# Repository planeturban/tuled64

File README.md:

# Totally Useless LED Programmer 64
### Wuuut?
It's just a useless way to use a RGB led as powerled in a C64. Why? Why not? It's pronounced TÖLP SIXTIFÅR since the author is from Sundsvall, Sweden.

# Hardware
The hardware is pretty much a stripped down Arduno Uno: an ATmega328p, an 16MHz xtal, two capacitors to piggyback on CIA2 of the C64. (The xtal and capacitors could be skipped, runnig at 8Mhz internal clock ought to be enough).

| Part | Footprint | Value |
|--|--|--|
| R1 | 1206 |Value depends on your led |
| R2 | 1206 |Value depends on your led |
| R3 |1206 |Value depends on your led |
| U1 | TQFP32 |ATMega 328P  |
| C1 | 1206 | Capacitor 22pf |
| C2 | 1206 | Capacitor 22pf |
| Y2 | HC49-US | Xtal 16MHz |

## Operation
Int1 (Arduino pin3 or ATmega pin1) is connected to  the port control (/PC) of CIA2, detecting when something is being sent from the C64 by attatching interrupt to falling state. This initializes the sequence counter interrupt function; not a pretty sight in the code, but it works. 

# Software
## 	Protocol
### Data 
| Byte | Data  |
|--|--|
|0-1  | Header: 0xff 0x99   |
| 2 | Data length, CMD + data  |
| 3 | CMD  |
| 4-n | Data, max 27 bytes  |
| n+1 | Checksum   0x100 - ((CMD + data) ^ 0xff) |

**The checksum part:**
CMD plus data is added together, xor'd and substracted from 256, let's say we're setting program speed to 10 (in blink mode: blink every 1 second). We'll be sending, header (0xff 0x99), length (0x02), set speed (0x03), speed itself (0x0a) and checksum (0x100 - ((0x03 + 0x0a) ^ 0xff) ).
| Byte | Data  |
|--|--|
|0|0xff|
|1|0x99|
|2|0x02|
|3|0x03|
|4|0x0a|
|5|0x0e|

### Commands

|Command| CMD |Size | Payload |
|--|--|--|--|
| Set RGB  | 0x01 | 3  | R, G, B value (0-255). Sets max value for all colors. |
| Set Mode | 0x02 | 1 | Mode, see "Mode table" |
| Set Speed | 0x03  | 1 | Speed: 10000 / X millis, used in fade, blink and others.  |
| Program select | 0x04 |1  | Program, 0-31. |
| Program save | 0x05 | 1 | Save to current program.  |
| Set color max | 0x06  | 2 | Color (Red = 0, Green = 1, Blue = 2), value (0-255) |
| Set color min | 0x07  | 2 | Color (Red = 0, Green = 1, Blue = 2), value (0-255) |
| Set program | 0x08  | 8 | Write program, see "Program" |
| Set start up program | 0x09 | 1 | Program number 0-31 |
| Next mode | 0x10 | - |  |
| Previous mode | 0x11  | -  |  |
| Next program | 0x12 | - |  |
| Previous program | 0x13 | - |  |
| Red + 1 | 0x14 | - |  |
| Red - 1 | 0x15 | - |  |
| Green + 1 | 0x16 | - |  |
| Green - 1 | 0x17 | - |  |
| Blue + 1 | 0x18 | - |  |
| Blue - 1 | 0x19 | - |  |
| Red + 10 | 0x1a | - |  |
| Red - 10 | 0x1b | - |  |
| Green + 10 | 0x1c | - |  |
| Green - 10 | 0x1d | - |  |
| Blue + 10 | 0x1e | - |  |
| Blue - 10 | 0x1f | - |  |
| Speed + 1 | 0x20 | - |  |
| Speed - 1 | 0x21 | - |  |
| Speed + 10 | 0x22 | - |  |
| Speed - 10 | 0x23 | - |  |
| Save current program | 0x24 | - |  |
| Write to EEPROM | 0x22 | 2 | Addr, data. |

## Programs

  32 programs are stored in EEPROM: 0-31 * 8 = 256 bytes
| Byte | Data | Explanation |
|--|--|--|
| 0 | Red max |  |
| 1 | Red min |  |
| 2 | Green max |  |
| 3 | Green min |  |
| 4 | Blue max |  |
| 5 | Blue min |  |
| 6 | Mode | |
| 7 | Speed | **10000 / X millis**, used in fade, blink and others. 39 millis is the fastest speed (10000/ 255), 10 seconds is the slowest. | 

## Arduino

### Configuration
#### Modes
When creating a new mode one have to update the maxMode byte and the switch statement in setup() adding a function call to the new mode function. 

A mode function is nothing but a loop that waits for exitLoop to become not zero. exitLoop is set in the interrupt routine if the command sent from the C64 was executed. **Good practice**: don't use *delay()* in  your mode.

modeZero(), just a normal static led. Sets the color and then goes into a loop.

    void modeZero() {
	  analogWrite(9, redMax);
	  analogWrite(10, greenMax);
	  analogWrite(11, blueMax);
	  while ( ! exitLoop ); // wait for next command.
	}

modeOne(), blinking led.

	void modeOne() {
	  unsigned long last = millis();
	  int ledStatus = 0;
	  while ( ! exitLoop ) {
	    if ( millis() - last >= (10000 / speed))  {
	      if ( ledStatus ) {
	        analogWrite(9, 0);
	        analogWrite(10, 0);
	        analogWrite(11, 0);
	        ledStatus = 0;
	      } else {
	        analogWrite(9, redMax);
	        analogWrite(10, greenMax);
	        analogWrite(11, blueMax);
	        ledStatus = 1;
	      }
	      last = millis();
	    }
	  }
	}

### FYI: How data is read.
As described in operetion an interrupt is attached, to read the data. However since there aren't 8 input pins available in a port the full byte sent from the C64 is pieced together using nibbles from PORTD and C. 

	void readData() {
	  value = (PIND & 0xF0) | (PINC & 0x0F); // Add nibbles to a byte.
	  if ( ! sequence && value == 0xff ) {
	    sequence++;
	    data[0] = value;
	  } else if ( sequence == 1 ) {
	    if ( value == 0x99 ) {
		      sequence++;
		      data[1] = value;
		      headerOk = 1;
		} else if ( value = 0xff ) {
	      // Just in case.. We might have gotten an extra 0xff from setting the serial port to output on the C64.
		} else {
		      sequence++;
		}
	  } else if ( sequence == 2 && headerOk ) {
	    sequence++;
	    len = value;
	    bytesLeft = value;
	    data[2] = value;
	    if ( len > 27 ) { // Payload too beaucoup
	      clearData();
	      sequence = 0;
	    }
	  } else if ( bytesLeft && sequence > 2) {
	    data[3 + ((bytesLeft * -1) + len)] = value;
	    bytesLeft--;
	  } else if ( ! bytesLeft && sequence > 2) {
	    checksum = value;
	    data[len + 3] = value;
	    if ( validateChecksum() ) {
			executeCommand();
	    } else {
			// Not a valid command, do nothing.
	    }
	    clearData();
	    sequence = 0;
	  } else { // Catch all.
	    clearData();
	    sequence = 0;
	  }
	}

### EEPROM layout

| Byte | Data | Explanation |
|--|--|--|
| 0-255 | Programs | As described above. |
| 257-508 | Reserved | |
| 509 | Program at start | Which program to run at start? 0-31 |
| 510 | Enable int0 | Enable interrupt on Arduino pin 2. |
| 511 | Version | Not implemented |

## C64
### Basic (yes, BASIC!) code
I'm using dustlayer as IDE so I'm not using row numbers in the example.

Setting speed to 10.

	rem set port to output
	poke 56579, 255 
	rem calculate checksum, 13 ^ 255 as described above.
	let chk = not 13 and 255
	let c = 256 - chk
	rem send header
	poke 56577, 255
	poke 56577, 153
	rem send length
	poke 56577, 2
	rem send command
	poke 56577, 3
	rem send data
	poke 56577, 10
	rem send checksum
	poke 56577, c
	rem port back to input.
	poke 56579, 0

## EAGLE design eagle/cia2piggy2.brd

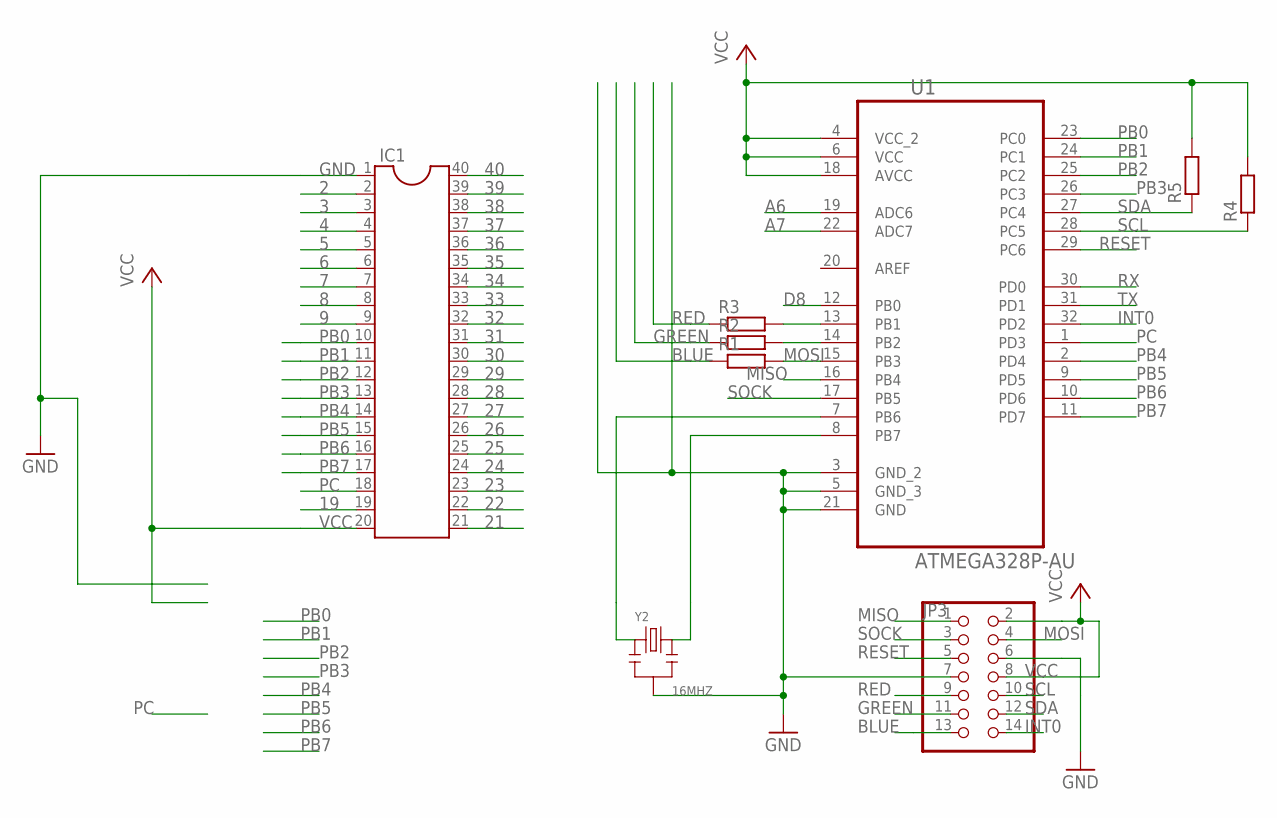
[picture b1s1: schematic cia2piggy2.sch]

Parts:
IC1: DIL40
JP3: PINHD-2X7; 2X07
R1, R2, R3, R4, R5: R-EU_M0805; M0805
U1: ATMEGA328P-AU; QFP80P900X900X120-32N
Y2: 16MHZ; X3-SMD-3.6X1.3X0.8MM

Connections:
2: IC1.2
3: IC1.3
4: IC1.4
5: IC1.5
6: IC1.6
7: IC1.7
8: IC1.8
9: IC1.9
19: IC1.19
21: IC1.21
22: IC1.22
23: IC1.23
24: IC1.24
25: IC1.25
26: IC1.26
27: IC1.27
28: IC1.28
29: IC1.29
30: IC1.30
31: IC1.31
32: IC1.32
33: IC1.33
34: IC1.34
35: IC1.35
36: IC1.36
37: IC1.37
38: IC1.38
39: IC1.39
40: IC1.40
A6: U1.19 (ADC6)
A7: U1.22 (ADC7)
BLUE: JP3.13, R1.1
D8: U1.12 (PB0)
GND: IC1.1, JP3.6, JP3.7, U1.3 (GND_2), U1.5 (GND_3), U1.21 (GND), Y2.2
GREEN: JP3.11, R2.1
INT0: JP3.14, U1.32 (PD2)
MISO: JP3.1, U1.16 (PB4)
MOSI: JP3.4, R1.2, U1.15 (PB3)
unnamed: R3.2, U1.13 (PB1)
unnamed: R2.2, U1.14 (PB2)
unnamed: U1.7 (PB6), Y2.1
unnamed: U1.8 (PB7), Y2.3
PB0: IC1.10, U1.23 (PC0)
PB1: IC1.11, U1.24 (PC1)
PB2: IC1.12, U1.25 (PC2)
PB3: IC1.13, U1.26 (PC3)
PB4: IC1.14, U1.2 (PD4)
PB5: IC1.15, U1.9 (PD5)
PB6: IC1.16, U1.10 (PD6)
PB7: IC1.17, U1.11 (PD7)
PC: IC1.18, U1.1 (PD3)
RED: JP3.9, R3.1
RESET: JP3.5, U1.29 (PC6)
RX: U1.30 (PD0)
SCL: JP3.10, R4.1, U1.28 (PC5)
SDA: JP3.12, R5.1, U1.27 (PC4)
SOCK: JP3.3, U1.17 (PB5)
TX: U1.31 (PD1)
VCC: IC1.20, JP3.2, JP3.8, R4.2, R5.2, U1.4 (VCC_2), U1.6 (VCC), U1.18 (AVCC)

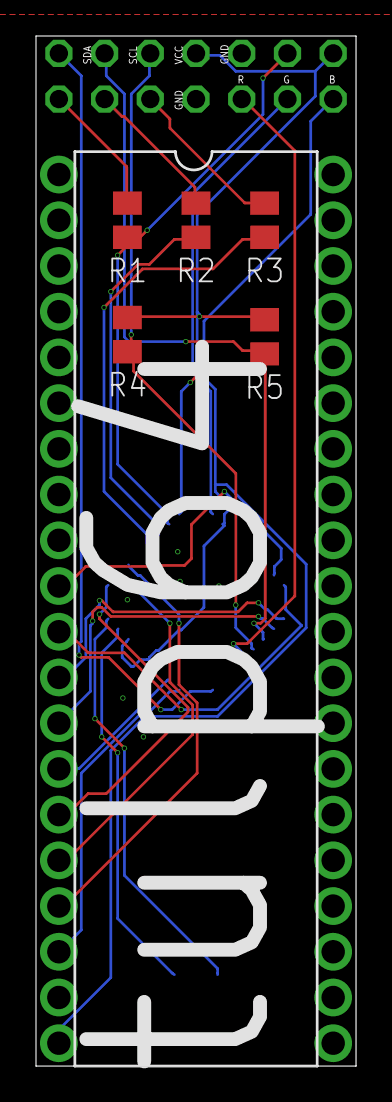
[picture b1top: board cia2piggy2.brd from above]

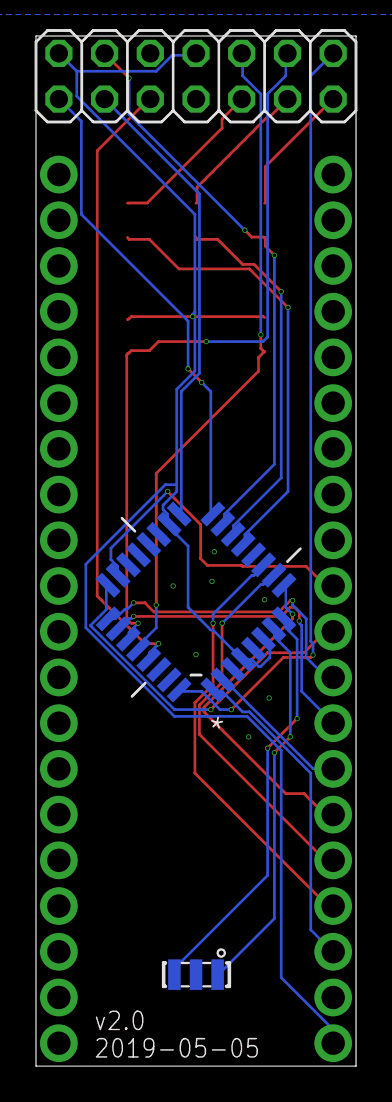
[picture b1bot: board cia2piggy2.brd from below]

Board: 2 copper layers, 17.8 x 57.2 mm, 9 parts (3 on the bottom side), 25 nets.

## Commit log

2019-05-02 First.
2019-05-02 readme. reeeedmeeeee Seymour
2019-05-02 Arduino code
2019-05-02 fixes. addition. stuff.
2019-05-02 led64.d64
2019-05-02 blank eeprom and so on..
2019-05-02 TÖLP
2019-05-03 color tune.
2019-05-05 more code.
2019-06-17 Eagle files
